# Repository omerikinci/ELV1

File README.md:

# ELV1 — Elektronik Kör Yük V1

Elektronik kör yük (electronic dummy load) cihazının ilk stabil versiyonu.
150 W ile sınırlandırılmış, 30 V / 10 A aralığını destekler.

Proje detayları ve görseller: https://omerikinci.com/projects/electronic-dummy-load

## İçerik

| Klasör | Açıklama |
| --- | --- |
| `firmware/` | STM32G030F6 için STM32CubeIDE projesi (`ilkdeneme`). Final kod: `firmware/Core/Src/main.c` |
| `firmware-history/2026-04-27-stable/` | 27.04.2026 tarihli önceki stabil `main.c` |
| `hardware/ELV1/` | KiCad şema ve PCB (`ELV1`, eski adıyla `Electronic Load`), PCB görselleri, projeye özel sembol kütüphanesi. Şema orijinal tasarımı gösterir; karttaki farklar aşağıda. |
| `hardware/ELV1-revision/` | ELV1'in revizyon kartı (tasarım aşamasında, STM32G071CBT6): KiCad şema ve PCB (`ELV1 revision`), G071 pin planı (`G071 pin plani.md`), firmware rehberi (`ELV1 revision - FIRMWARE REHBERI.txt`), görseller |
| `hardware/libraries/` | Projelerde kullanılan özel KiCad sembol (`symbols/`) ve footprint (`footprints/`) kütüphaneleri |
| `arduino-prototype/` | STM32'ye geçmeden önceki Arduino tabanlı ilk prototip (`koryukprojesi.ino`) |

## Firmware

- MCU: STM32G030F6Px
- ADS1115 (I2C) ile akım/gerilim ölçümü, dahili ADC
- DS18B20 sıcaklık sensörü
- I2C LCD, buzzer, soft-start

Derlemek için `firmware/` klasörünü STM32CubeIDE'ye mevcut proje olarak içe aktarın.

## ELV1'in final hali (şemadan farklar)

ELV1 ilk cihazdır ve bu haliyle kalır. Sorunlar anlaşıldıkça yalnızca düzeltme yapılır.
Yeni özellikler (USB/PC bağlantısı, pot yerine encoder vb.) ELV1 revision'a aittir.

`hardware/ELV1/ELV1.kicad_sch` **bilerek güncellenmedi**; orijinal tasarımı gösterir
(4 MOSFET, 4 x 0.1 Ω şönt, LM358). Karttaki gerçek durum:

| Parça | Şemada | Kartta | Tarih |
| --- | --- | --- | --- |
| Yük MOSFET'leri | U1, U6, U12, U13 (4 x IRFP260N) | Yalnız U1 ve U6. U12, U13 söküldü. | 10.2026 |
| Şöntler | R2, R23, R30, R45: 0.1 Ω 10 W (markasız) | R2 ve R23 yerinde: 2 x Isabellenhütte VMS-R100-1.0-U paralel = 0.05 Ω. R30, R45 söküldü. | 20.10.2026 |
| Op-amp'ler (U2, U3) | LM358 | OPA2197 | — |
| R1 (akım potu besleme direnci) | 440K | 440K olmalı (aşağıdaki nota bak) | 20.10.2026 |
| Şebeke X kondansatörü boşaltması | yok | 1 MΩ 1 W THT, AC girişte L-N arası | 20.10.2026 |

**Neden:**
- **Şöntler:**
  - Markasız 10 W dirençler ısındıkça akım kayıyordu. VMS'nin sıcaklık katsayısı < 20 ppm/K.
  - 2 MOSFET'te tek 0.1 Ω VMS, 5 A'de 2.5 W harcar; bu, 3 W sınırının %83'üdür ve direnç aşırı ısınıyordu.
  - Paralel çiftte direnç başına 0.625 W düşer (sınırın %21'i).
- **R1:**
  - Akımı pot ayarlar. Op-amp her şöntün gerilimini pot gerilimine eşitler, bu yüzden toplam akım = kanal sayısı x pot gerilimi / şönt direnci.
  - 2 x 0.1 Ω döneminde pot tam turda ~5 A veriyordu. Bu yüzden R1 geçici olarak 220K yapıldı.
  - 2 x 0.05 Ω ile 440K tekrar tam turda ~10 A verir; bu, orijinal 4 x 0.1 Ω ölçeğidir.
  - 220K ile tam tur ~20 A ister ve ISET % göstergesi yarı turda %100'e ulaşır.
- **Boşaltma direnci:**
  - Cihaz kapalıyken fiş çekilince EMI filtresinin X kondansatöründe kalan şarj çarpıyordu.
  - Önce geçici olarak 12 x 10 MΩ paralel (~790k) takıldı. Ancak paralel bağlı her direnç tam şebeke tepe gerilimini (~325 V) görür; 1/8 ve 1/4 W dirençler bu gerilim için uygun değil.
  - 20.10.2026'da bunların yerine tek 1 MΩ, 1 W, 500 V direnç (Royalohm MF02WJJ0105A19) takıldı.

**Durum (20.10.2026):** ELV1 tamamlandı. Bir sorun çıkmadıkça açılmayacak; geliştirme ELV1 revision'da sürüyor.

**Firmware'de buna göre ayarlananlar** (`firmware/Core/Src/main.c`):
- Akım, iki kanalın tek uçlu okumalarının toplamıdır: ADS1115 AIN0 (U1) + AIN1 (U6), `CURRENT_ADS_CH_MASK 0x03`.
  - ±0.512 V aralık, 250 SPS, kanal başına 8 örnek ortalaması.
  - Kelvin bağlantısı yok. Her kanal şöntle birlikte ortak GND yolunun düşümünü de görür. Bu düşüm `CURRENT_UV_PER_A 59172` (0.05 Ω + 2 x ~4.6 mΩ) katsayısının içindedir.
  - Kalibrasyon: seri multimetreyle ~5 A'de karşılaştır, yeni = 59172 x (ekrandaki / multimetredeki).
- Diğer ayarlar:
  - SET V düşük koruması 10 mA'den itibaren devrede.
  - Ekrandaki gerilimler kesilmez, yuvarlanır.
  - Güç koruması 160 W (MOSFET başına ~80 W).

**Ölçülen özellikler:**
- Ters polarite algılaması 1.71 V'ta devreye giriyor.

## ELV1 revision'ı başka bilgisayarda açmak (Windows / macOS)

1. Repoyu klonla:
   ```
   git clone https://github.com/omerikinci/ELV1.git
   ```
2. KiCad 10 ile `hardware/ELV1-revision/ELV1 revision.kicad_pro` dosyasını aç.
3. Özel kütüphaneler artık **global** tablodan yükleniyor (18.10.2026). Proje-içi
   `sym-lib-table` / `fp-lib-table` dosyaları kaldırıldı, çünkü global tabloda aynı
   isimler tanımlıyken KiCad çakışma uyarısı veriyordu.

   Yeni bir bilgisayarda kurulum: `hardware/libraries/` içeriğini kalıcı bir yere kopyala
   (bu makinede `~/Documents/Elektronik/Library/`), sonra KiCad'de
   **Preferences → Manage Symbol Libraries / Manage Footprint Libraries → Global**
   sekmesine şu isimlerle ekle:

   | Sembol kütüphanesi | Footprint kütüphanesi |
   | --- | --- |
   | `myCONN`, `myCPU`, `myDiodes`, `myIC`, `myNMOS`, `myNTC`, `mySW` | `myNTC`, `myTO247`, `myFuse` |

   Dikkat: eski isimler `my-NMOS` ve `mydiodes` kullanımdan kalktı; sırasıyla `myNMOS`
   ve `myDiodes` oldu. `hardware/libraries/` sürüm kontrolündeki asıl kaynaktır —
   global kopyayı ondan tazele, ters yönde değil.
4. Çalışmaya başlamadan önce `git pull`, bitirince `git add` / `git commit` / `git push` yap.
   İki bilgisayarda aynı anda aynı dosyayı düzenleme; KiCad dosyaları birleştirilemez.

Not: `*-backups/`, `*.kicad_prl`, `fp-info-cache` ve kilit dosyaları `.gitignore` ile dışarıda tutulur.

Bu makinedeki konum: `~/Documents/GitHub/ELV1-revision/` — GitHub Desktop'ın yönettiği
klasörde, `ELV2` deposunun yanında. Bu repo git üzerinden çalışılır; KiCad projeleri
`hardware/` altında.

`~/Documents/Elektronik/Projeler/ElectronicLoad/` orada duran ayrı bir kopyadır ve bu
repodaki `hardware/ELV1/` ile aynı kartın eski adıdır — hangisinin kalacağına karar
verilmedi.

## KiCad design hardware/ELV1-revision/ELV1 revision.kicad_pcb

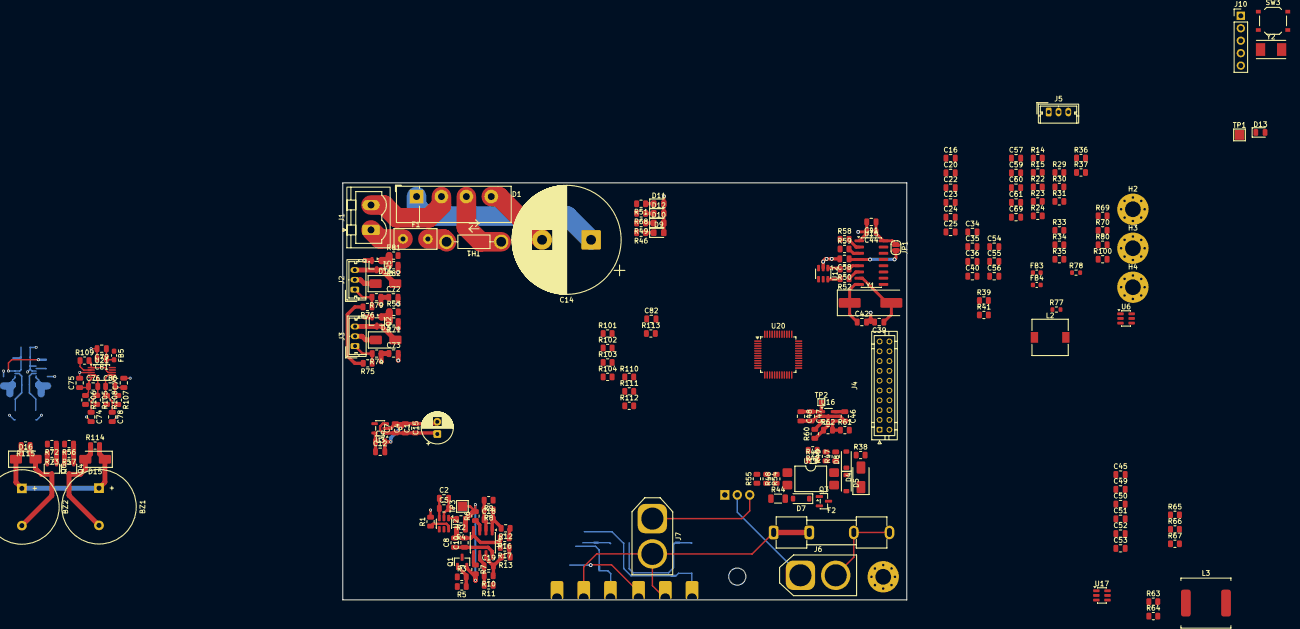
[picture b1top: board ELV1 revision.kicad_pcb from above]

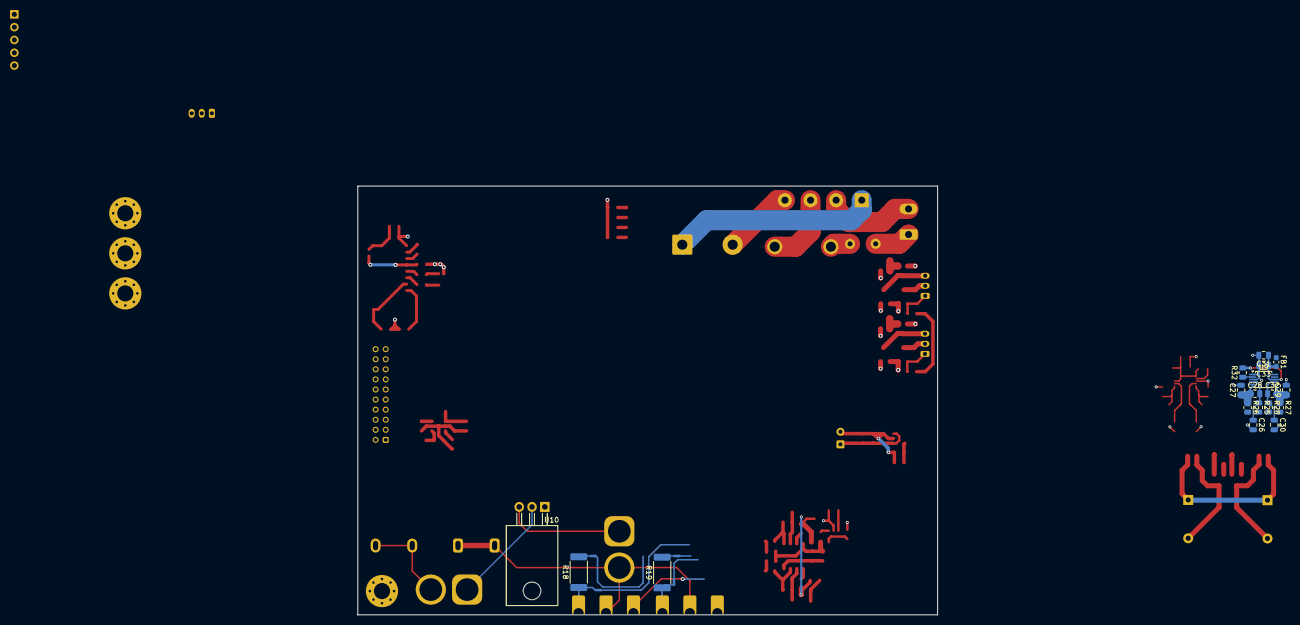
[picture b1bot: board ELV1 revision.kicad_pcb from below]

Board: 2 copper layers, 115.0 x 85.1 mm, 228 parts (22 on the bottom side), 124 nets.

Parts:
BZ1, BZ2: Passive Buzzer; Buzzer_15x7.5RM7.6
C1, C16, C31, C41, C45, C46, C48, C79: 10uF X7R; C_0805_2012Metric
C2: 10uF; C_0805_2012Metric
C4, C8, C9: 1uF X7R; C_0805_2012Metric
C5, C57, C59, C60, C69: 100nF; C_0805_2012Metric
C7, C10, C12, C20, C22, C33, C34, C35, C36, C40, C44, C47, C49, C50, C58, C81, C82: 100nF X7R; C_0805_2012Metric
C14: 6800uF; CP_Radial_D22.0mm_P10.00mm_SnapIn
C15: 100uF; CP_Radial_D6.3mm_P2.50mm
C18, C19, C72, C73: 10nF; C_0805_2012Metric
C23, C24, C51, C52: 22uF; C_0805_2012Metric
C25: 75pF; C_0805_2012Metric
C26, C27, C29, C30, C74, C75, C77, C78: 22nF X7R; C_0805_2012Metric
C28, C32, C76, C80: 220nF X7R; C_0805_2012Metric
C39, C42: 22pF NP0; C_0805_2012Metric
C53: 100pF; C_0805_2012Metric
C54, C55: 22pF; C_0805_2012Metric
C56: 1uF; C_0805_2012Metric
C61: 4.7uF; C_0805_2012Metric
D1: KBU8M; Diode_Bridge_Vishay_KBU
D3, D14, D15, D16: SS14; D_SMA
D4: 12V ZENER; D_SMA
D5, D7, D8: 1N4148W; D_SOD-123
D9, D10, D11, D12: RED LED; LED_0805_2012Metric_Pad1.15x1.40mm_HandSolder
D13: STATUS LED; LED_0805_2012Metric
F1: 2A Slow Blow; Fuse_Littelfuse_395Series
F2: 15A FUSE; Fuseholder_Clip-5x20mm_Keystone_3512_Inline_P23.62x7.27mm_D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
FB1, FB5: 600R 100MHz; L_0603_1608Metric_Pad1.05x0.95mm_HandSolder
FB3, FB4: 600R 100MHZ; L_0603_1608Metric
H1, H2, H3, H4: MountingHole_Pad; MountingHole_3.2mm_M3_Pad_Via
J1: 15VAC 30VA Transformer out; PhoenixContact_MSTBVA_2,5_2-G-5,08_1x02_P5.08mm_Vertical
J2: FAN1; Molex_Micro-Latch_53253-0370_1x03_P2.00mm_Vertical
J3: FAN2; Molex_Micro-Latch_53253-0370_1x03_P2.00mm_Vertical
J4: Conn_02x10_Odd_Even; JST_PHD_B20B-PHDSS_2x10_P2.00mm_Vertical
J5: DS18B20; Molex_Micro-Latch_53253-0370_1x03_P2.00mm_Vertical
J6, J7: power in (outside); AMASS_XT60-M_1x02_P7.20mm_Vertical
J10: PROGRAM PINS; PinHeader_1x05_P2.54mm_Vertical
JP1: SolderJumper_2_Open; SolderJumper-2_P1.3mm_Open_RoundedPad1.0x1.5mm
L2: 10uH; L_7.3x7.3_H4.5
L3: 15uH; L_SOREDE_SNR.1050_10x10x5mm
NT1, NT2, NT3, NT4: NetTie_2; NetTie-2_SMD_Pad0.5mm
Q1, Q2, Q3, Q5: IRLML6344TRPBF; SOT-23
Q4, Q6: IRLML6344TRPBF; SOT-23-3
R1, R2, R5, R16, R17, R29, R32, R34, R42, R57, R71, R73, R74, R75, R76, R79, R82, R100, R109: 10K; R_0805_2012Metric
R3, R12, R13, R25, R26, R27, R28, R40, R41, R56, R58, R59, R70, R72, R105, R106, R107, R108: 100R; R_0805_2012Metric
R4: 2.2K; R_0805_2012Metric
R6, R7, R9, R11, R30, R35, R36, R37, R49, R53, R61, R81, R114, R115: 1K; R_0805_2012Metric
R8, R10: 220K; R_0805_2012Metric
R14, R63: 511K; R_0805_2012Metric
R15, R64: 105K; R_0805_2012Metric
R18, R19: 0.1R SHUNT RESISTOR; R_2512_6332Metric_Pad1.40x3.35mm_HandSolder
R22, R65: 49.9R; R_0805_2012Metric
R23, R38, R48, R62, R66, R112: 100K; R_0805_2012Metric
R24: 13K; R_0805_2012Metric
R31, R33, R39, R51, R68, R69, R110, R111: 4.7K; R_0805_2012Metric
R44: 5.6K; R_1206_3216Metric
R45: 47K; R_0805_2012Metric
R46, R80: 330R; R_0805_2012Metric
R47: 100; R_0805_2012Metric
R50, R52: 22R; R_0805_2012Metric
R54, R101, R103: 47K 0.1%; R_0805_2012Metric
R55, R102, R104: 3.3K 0.1%; R_0805_2012Metric
R60: 3.3K; R_0805_2012Metric
R67: 5.23K; R_0805_2012Metric
R77, R78: 0R; R_0603_1608Metric
R113: 12K; R_0805_2012Metric
SW3: SW_Push; SW_Push_1P1T_XKB_TS-1187A
TH1: 0R; NTC
TP1, TP3: TestPoint; TestPoint_Pad_2.0x2.0mm
TP2: TestPoint; TestPoint_Pad_1.0x1.0mm
U2: MCP4725xxx-xCH; SOT-23-6
U3: AP2112K-3.3; SOT-23-5
U4: OPA2197xD; SOIC-8_3.9x4.9mm_P1.27mm
U6, U17: TPS54302; SOT-23-6
U7, U8: IRFP260NPBF; TO-247 Edge Castellated
U9, U21: ADS1115IDGS; TSSOP-10_3x3mm_P0.5mm
U10: IRFB4110PBF; TO-220-3_Horizontal_TabDown
U12: SRV05-4; SOT-23-6
U13: LTV-817S; SMDIP-4_W9.53mm
U15: CH340G; SOIC-16_3.9x9.9mm_P1.27mm
U16: SY6280AAC; SOT-23-5_HandSoldering
U20: STM32G071CBT6; LQFP-48_7x7mm_P0.5mm
Y1: 12MHZ CRYSTAL; Crystal_SMD_HC49-SD
Y2: ABM7-8.000MHZ-D2Y-T; Crystal_SMD_Abracon_ABM7-2Pin_6.0x3.5mm

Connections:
+3.3V: C2.1, C5.1, C9.1, C12.1, C41.1, C44.1, C59.1, FB1.1, FB3.1, FB4.2, FB5.1, J4.1, J4.16, J5.1, J10.1, JP1.1 (A), R5.2, R30.1, R31.2, R33.2, R34.2, R39.2, R42.1, R45.2, R46.2, R69.2, R75.2, R76.2, R100.2, R110.2, R111.2, U2.3 (VDD), U3.5 (VOUT), U15.16 (VCC), U20.4 (VBAT)
+5V: BZ1.1 (+), BZ2.1 (+), C1.1, C4.1, C7.1, C15.1, C23.1, C24.1, C46.1, D15.1 (K), D16.1 (K), J4.3, L2.2, R22.1, R49.2, R114.2, R115.2, U3.1 (VIN), U3.3 (EN), U16.5 (IN)
+12V: C8.1, C10.1, C51.1, C52.1, D3.1 (K), D14.1 (K), J2.2, J3.2, L3.2, R65.1, R68.2, U4.8 (V+)
/20V: C14.1, C16.1, C20.1, C45.1, C49.1, D1.1 (+), R14.1, R51.2, R63.1, R112.2, U6.3 (VIN), U17.3 (VIN)
/20V SENSE: C82.1, R112.1, R113.2, U20.11 (PA0)
/ADS2 VDD: C79.1, C81.1, FB5.2, R109.2, U21.1 (ADDR), U21.8 (VDD)
/AR0: NT1.1, R9.1, R25.2
/AR1: NT2.1, R26.2
/AR2: NT3.1, R11.1, R27.2
/AR3: NT4.1, R28.2
/BUZZER1: R56.2, U20.17 (PA6)
/BUZZER2: R72.2, U20.18 (PA7)
/D+: J4.10, R50.2, U12.1 (IO1)
/D-: J4.12, R52.2, U12.6 (IO4)
/DAC CONTROL: R3.1, U20.30 (PC6)
/DS18B20 DQ: R41.2, R70.1, U20.23 (PB11)
/ENDODER A: C35.1, R36.1, U20.25 (PB13)
/ENDODER B: C34.1, R35.1, U20.26 (PB14)
/ENDODER SW: C36.1, R37.1, U20.27 (PB15)
/FAN CONTROL 1: R81.2, U20.48 (PB9)
/FAN CONTROL 2: R53.2, U20.22 (PB10)
/G1: R12.1, R16.1, U7.1 (G)
/G2: R13.1, R17.1, U8.1 (G)
/I2C SCL: J4.5, R110.1, U2.5 (SCL), U9.10 (SCL), U20.33 (PA9/PA11), U21.10 (SCL)
/I2C SDA: J4.7, R111.1, U2.4 (SDA), U9.9 (SDA), U20.34 (PA10/PA12), U21.9 (SDA)
/LOAD VOLTAGE: C40.1, R54.1, R55.2, R105.2, R108.2, U20.14 (PA3)
/OUT CONTROL: R40.1, R42.2, U20.24 (PB12)
/RCP: R47.2, U20.13 (PA2)
/RESET BUTTON: J4.13, R29.1, U20.31 (PC7)
/RX: R58.1, U20.46 (PB7)
/TACT1: C72.1, R79.1, U20.43 (PB4)
/TACT2: C73.1, R74.1, U20.44 (PB5)
/TX: R59.1, U20.45 (PB6)
/USB 5V: C47.1, C48.1, J4.17, TP2.1 (1_1), U16.1 (OUT)
/USB CHARGE: R61.2, U20.37 (PA15)
/VCC LINE: F2.1, J7.2, R103.2, U7.2 (D), U8.2 (D)
/VLINE DIV: R103.1, R104.2, R107.2
/VS-: R101.1, R102.2, R106.2
GND: C1.2, C2.2, C4.2, C5.2, C7.2, C8.2, C9.2, C10.2, C12.2, C14.2, C15.2, C16.2, C20.2, C23.2, C24.2, C26.2, C27.2, C29.2, C30.2, C31.2, C33.2, C34.2, C35.2, C36.2, C39.2, C40.2, C41.2, C42.2, C44.2, C45.2, C46.2, C47.2, C48.2, C49.2, C51.2, C52.2, C54.1, C55.1, C56.2, C57.2, C58.2, C59.2, C60.2, C61.2, C69.2, C72.2, C73.2, C74.2, C75.2, C77.2, C78.2, C79.2, C81.2, C82.2, D1.4 (-), D4.2 (A), D9.2 (A), D10.2 (A), D11.2 (A), D12.2 (A), D13.1 (K), J4.8, J4.9, J4.14, J4.15, J4.19, J4.20, J5.3, J7.1, J10.5, NT2.2, NT4.2, Q1.3 (D), Q2.2 (S), Q3.3 (D), Q4.2 (S), Q5.2 (S), Q6.2 (S), R1.2, R4.2, R15.2, R16.2, R17.2, R18.2, R19.2, R24.2, R29.2, R55.1, R57.2, R60.1, R62.1, R64.2, R67.2, R71.1, R73.2, R82.1, R102.1, R104.1, R113.1, SW3.1, U2.2 (VSS), U3.2 (GND), U4.4 (V-), U6.1 (GND), U9.1 (ADDR), U9.3 (GND), U10.3 (S), U12.2 (VN), U13.3, U15.1 (GND), U16.2 (GND), U17.1 (GND), U20.7 (VSS), U21.3 (GND)
GND1: J6.1, R44.1, R101.2, U10.2 (D)
unnamed: BZ1.2 (-), D15.2 (A), Q4.3 (D), R114.1
unnamed: BZ2.2 (-), D16.2 (A), Q6.3 (D), R115.1
unnamed: C18.2, R8.1, R12.2, U4.1
unnamed: C19.2, R10.1, R13.2, U4.7
unnamed: C25.1, R22.2, R23.1
unnamed: C53.1, R65.2, R66.1
unnamed: C54.2, R77.1, Y2.2
unnamed: C55.2, R78.1, Y2.1
unnamed: D1.3, TH1.1
unnamed: D3.2 (A), J3.3, Q2.3 (D)
unnamed: D4.1 (K), D5.2 (A), Q3.2 (S), R38.1, U10.1 (G)
unnamed: D5.1 (K), D8.1 (K), U13.4
unnamed: D7.2 (A), R44.2
unnamed: D7.1 (K), R48.2, U13.1
unnamed: D8.2 (A), R45.1, R47.1
unnamed: D9.1 (K), R46.1
unnamed: D10.1 (K), R49.1
unnamed: D11.1 (K), R51.1
unnamed: D12.1 (K), R68.1
unnamed: D13.2 (A), R80.1
unnamed: D14.2 (A), J2.3, Q5.3 (D)
unnamed: F1.2, TH1.2
unnamed: F1.1, J1.1
unnamed: D1.2, J1.2
unnamed: J2.1, R76.1, R79.2
unnamed: J3.1, R74.2, R75.1
unnamed: J4.2, R31.1, R35.2
unnamed: J4.4, R33.1, R36.2
unnamed: J4.6, R34.1, R37.2
unnamed: J4.11, R30.2
unnamed: J4.18, R39.1, R41.1
unnamed: J5.2, R69.1, R70.2
unnamed: F2.2, J6.2, R48.1, R54.2, U13.2
unnamed: J10.2, U20.35 (PA13)
unnamed: J10.3, U20.36 (PA14)
unnamed: C69.1, J10.4, R100.1, SW3.2, U20.10 (PF2)
unnamed: C58.1, JP1.2 (B), U15.4 (V3)
unnamed: Q1.1 (G), R3.2, R5.1
unnamed: Q1.2 (S), R2.1, R4.1, R6.2, R7.2, TP3.1 (1_1)
unnamed: Q2.1 (G), R53.1, R71.2
unnamed: Q3.1 (G), R40.2
unnamed: Q4.1 (G), R56.1, R57.1
unnamed: Q5.1 (G), R81.1, R82.2
unnamed: Q6.1 (G), R72.1, R73.1
unnamed: R1.1, U2.6 (A0)
unnamed: R2.2, U2.1 (VOUT)
unnamed: R6.1, U4.3 (+)
unnamed: C18.1, R8.2, R9.2, U4.2 (-)
unnamed: R7.1, U4.5 (+)
unnamed: C19.1, R10.2, R11.2, U4.6 (-)
unnamed: C22.1, U6.6 (BOOT)
unnamed: R14.2, R15.1, U6.5 (EN)
unnamed: C25.2, R23.2, R24.1, U6.4 (FB)
unnamed: C22.2, L2.1, U6.2 (SW)
unnamed: NT1.2, R18.1, U7.3 (S)
unnamed: NT3.2, R19.1, U8.3 (S)
unnamed: C26.1, C28.2, R25.1, U9.4 (AIN0)
unnamed: C27.1, C28.1, R26.1, U9.5 (AIN1)
unnamed: C29.1, C32.2, R27.1, U9.6 (AIN2)
unnamed: C30.1, C32.1, R28.1, U9.7 (AIN3)
unnamed: R32.1, U9.2 (ALERT/RDY)
unnamed: C31.1, C33.1, FB1.2, R32.2, U9.8 (VDD)
unnamed: R59.2, U15.3 (RXD)
unnamed: R58.2, U15.2 (TXD)
unnamed: R50.1, U15.5 (UD+)
unnamed: R52.1, U15.6 (UD-)
unnamed: C39.1, U15.7 (XI), Y1.2
unnamed: C42.1, U15.8 (XO), Y1.1
unnamed: R61.1, R62.2, U16.4 (EN)
unnamed: R60.2, U16.3 (ISET)
unnamed: C50.1, U17.6 (BOOT)
unnamed: R63.2, R64.1, U17.5 (EN)
unnamed: C53.2, R66.2, R67.1, U17.4 (FB)
unnamed: C50.2, L3.1, U17.2 (SW)
unnamed: R80.2, U20.19 (PB0)
unnamed: R77.2, U20.8 (PF0)
unnamed: R78.2, U20.9 (PF1)
unnamed: C60.1, C61.1, FB4.1, TP1.1 (1_1), U20.6 (VDD)
unnamed: C56.1, C57.1, FB3.2, U20.5 (VREF+)
unnamed: C74.1, C76.2, R105.1, U21.4 (AIN0)
unnamed: C75.1, C76.1, R106.1, U21.5 (AIN1)
unnamed: C77.1, C80.2, R107.1, U21.6 (AIN2)
unnamed: C78.1, C80.1, R108.1, U21.7 (AIN3)
unnamed: R109.1, U21.2 (ALERT/RDY)

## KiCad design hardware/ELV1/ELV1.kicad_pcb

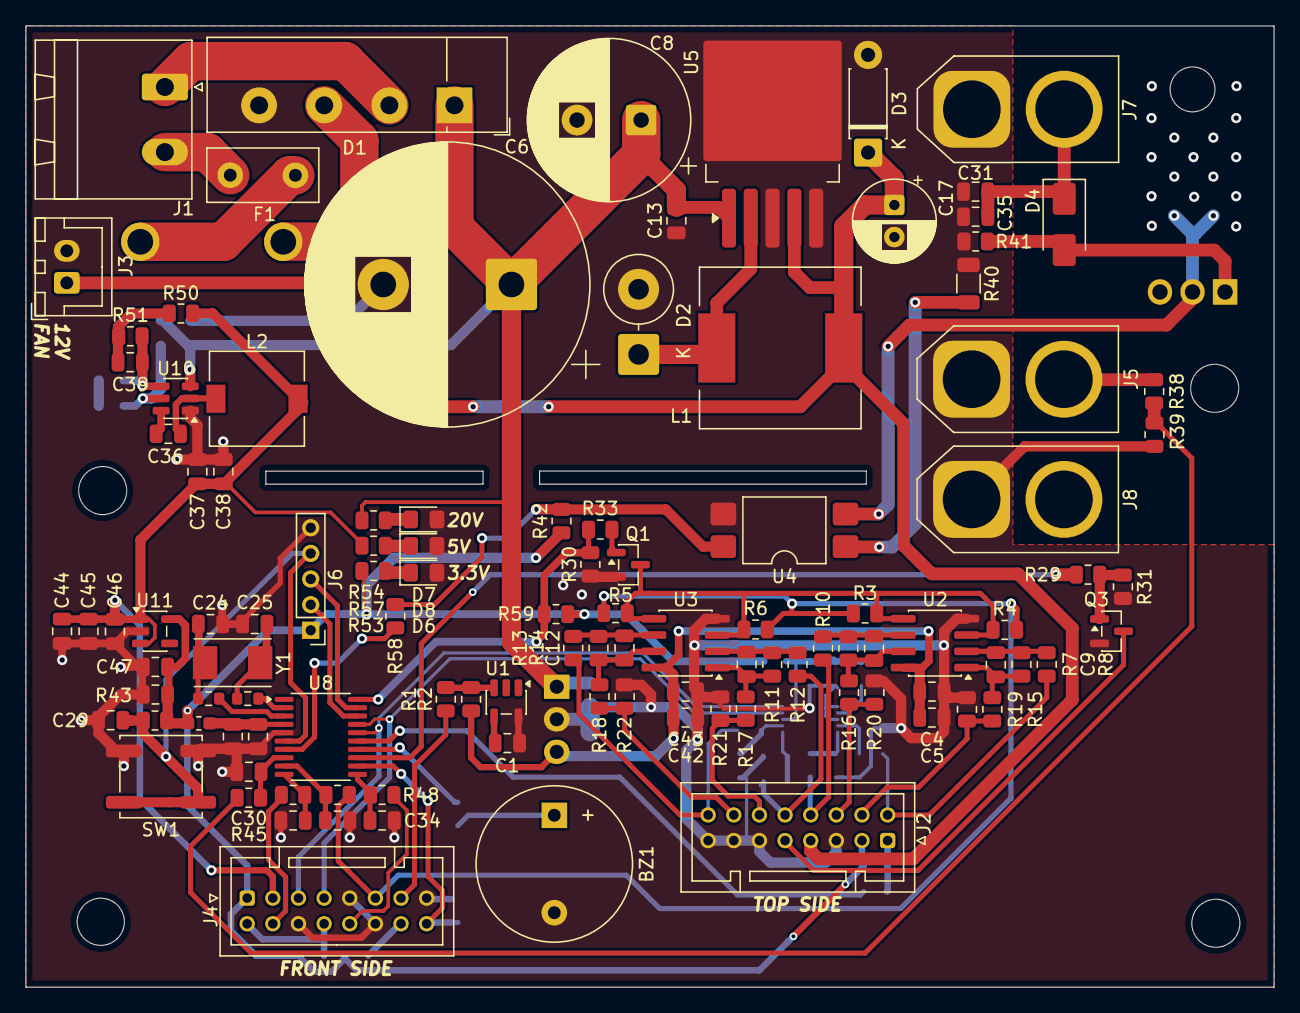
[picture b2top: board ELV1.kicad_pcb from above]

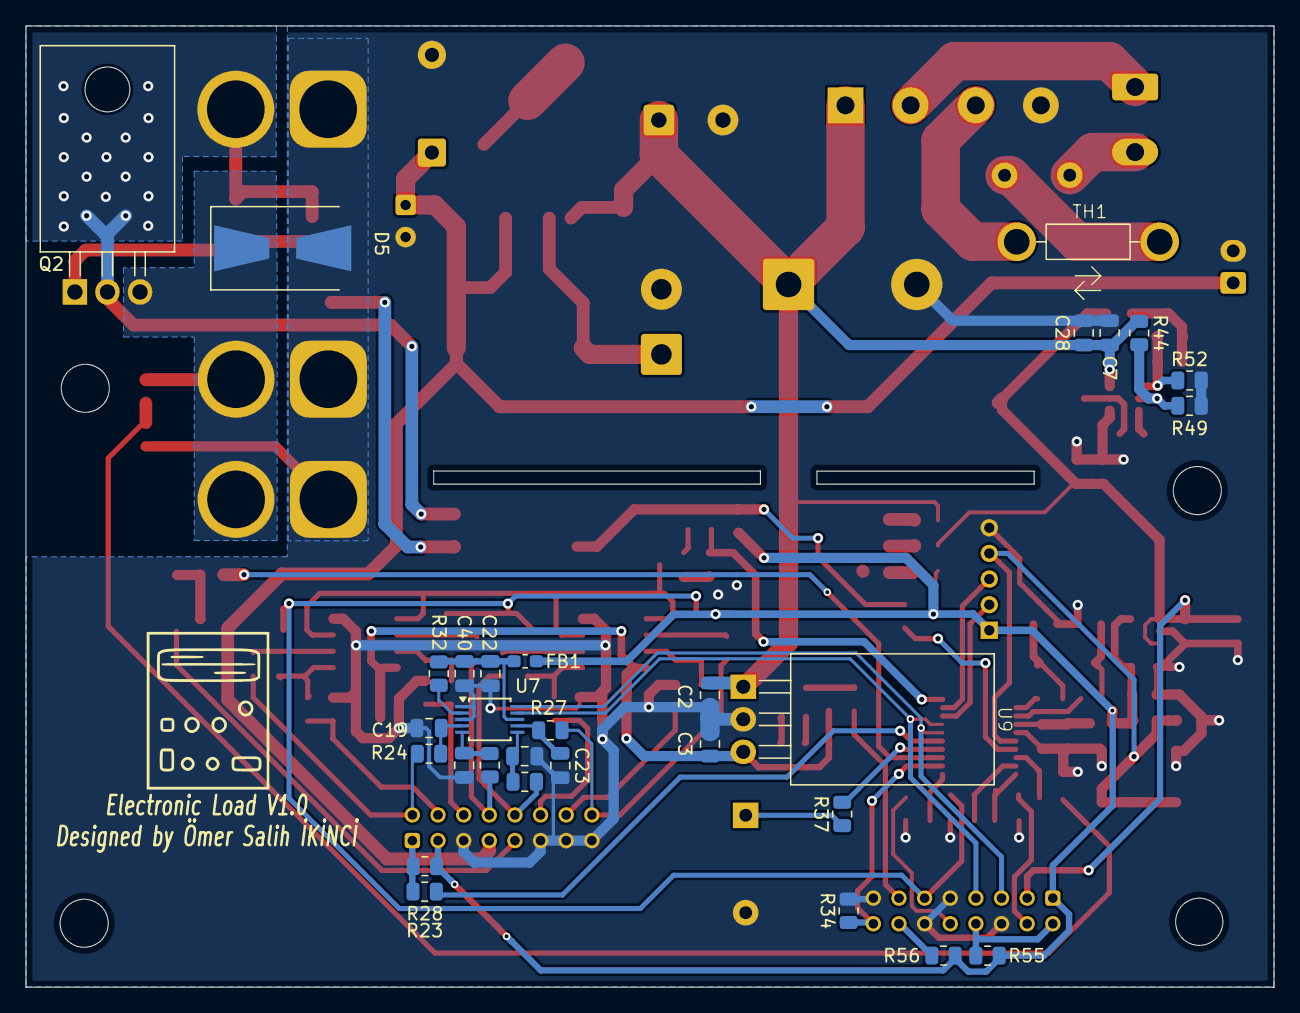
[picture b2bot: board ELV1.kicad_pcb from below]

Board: 2 copper layers, 97.3 x 75.0 mm, 140 parts (30 on the bottom side), 81 nets.

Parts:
BZ1: Buzzer; Buzzer_12x9.5RM7.6
C1, C26, C28, C40, C44: 10uF X7R; C_0805_2012Metric
C2, C3, C5, C7, C13, C19, C20, C21, C22, C23, C27, C29, C30, C32, C33, C34, C36, C42, C45, C48: 100nF X7R; C_0805_2012Metric
C4, C31, C43, C46, C47: 1uF X7R; C_0805_2012Metric
C6: 6800uF; CP_Radial_D22.0mm_P10.00mm_SnapIn
C8: 680uF 50V; CP_Radial_D12.5mm_P5.00mm
C9, C10, C11, C12: 1nF; C_0805_2012Metric
C17: 220uF 25V; CP_Radial_D6.3mm_P2.50mm
C24, C25: 18pF; C_0805_2012Metric
C35: 100nF 63V; C_0805_2012Metric
C37, C38: 22uF; C_0805_2012Metric
C39: 75pF; C_0805_2012Metric
D1: KBU8M; Diode_Bridge_Vishay_KBU
D2: 1N5822; D_DO-201AD_P5.08mm_Vertical_KathodeUp
D3: 1N4007; D_DO-41_SOD81_P7.62mm_Horizontal
D4: 12V ZENER; D_SMA
D5: SMCJ33CA-TKS; D_SMB-SMC_Universal_Handsoldering
D6, D7, D8: RED LED; LED_0805_2012Metric_Pad1.15x1.40mm_HandSolder
F1: 2A Slow Blow; Fuse_Littelfuse_395Series
FB1, FB2: 600R 100MHz; L_0603_1608Metric_Pad1.05x0.95mm_HandSolder
J1: 15VAC Transformer out; PhoenixContact_MSTBA_2,5_2-G-5,08_1x02_P5.08mm_Horizontal
J2: Top Panel; JST_PUD_B16B-PUDSS_2x08_P2.00mm_Vertical
J3: FAN OUT; JST_XH_B2B-XH-A_1x02_P2.50mm_Vertical
J4: Front Panel; JST_PUD_B16B-PUDSS_2x08_P2.00mm_Vertical
J5: power in (inside); AMASS_XT60-M_1x02_P7.20mm_Vertical
J6: Program Pins; PinHeader_1x05_P2.00mm_Vertical
J7: power in (outside); AMASS_XT60-M_1x02_P7.20mm_Vertical
J8: power in (outside) for batteries; AMASS_XT60-M_1x02_P7.20mm_Vertical
L1: 33uH; L_12x12mm_H8mm
L2: 10uH; L_7.3x7.3_H4.5
Q1, Q3: IRLML6344TRPBF; SOT-23
Q2: IRF4905; TO-220F-3_Horizontal_TabDown
R1: 22K; R_0805_2012Metric
R2, R19, R20, R21, R22, R30, R31, R32, R34, R42, R43, R59: 10K; R_0805_2012Metric
R3, R4, R5, R6, R8, R10, R12, R14, R24, R25, R26, R27, R41, R45, R46, R47, R48, R54, R55, R56: 1K; R_0805_2012Metric
R7, R9, R11, R13: 220K; R_0805_2012Metric
R15, R16, R17, R18, R23, R33, R37, R57: 100R; R_0805_2012Metric
R28: 4.7K; R_0805_2012Metric
R29, R58: 100; R_0805_2012Metric
R35, R36: 0R; R_0603_1608Metric
R38: 470K; R_0805_2012Metric
R39: 33K; R_0805_2012Metric
R40: 5.6K; R_1206_3216Metric
R44: 511K; R_0805_2012Metric
R49: 105K; R_0805_2012Metric
R50: 49.9R; R_0805_2012Metric
R51: 100K; R_0805_2012Metric
R52: 13.3K; R_0805_2012Metric
R53: 10R; R_0805_2012Metric
SW1: SW_Push_1P1T_NO_CK_KSC7xxJ
TH1: NTC 10R; NTC
U1: TL431DBV; SOT-23-5
U2, U3: LM358; SOIC-8_3.9x4.9mm_P1.27mm
U4: LTV-817S; SMDIP-4_W9.53mm
U5: LM2596S-12; TO-263-5_TabPin3
U7: ADS1115IDGS; TSSOP-10_3x3mm_P0.5mm
U8: STM32G030F6Px; TSSOP-20_4.4x6.5mm_P0.65mm
U9: LM7815_TO220; myto220
U10: TPS54302; SOT-23-6
U11: AP2112K-3.3; SOT-23-5
Y1: 8mHz; Crystal_SMD_Abracon_ABM7-2Pin_6.0x3.5mm

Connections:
/3.3V: C47.1, C48.1, FB1.1, FB2.1, J2.3, J4.1, J6.1, R28.1, R42.2, R43.2, R53.2, R55.1, R56.1, R59.1, U11.5 (VOUT)
/5V: C37.1, C38.1, C44.1, C45.1, C46.1, J4.3, L2.2, R50.1, R57.2, U11.1 (VIN), U11.3 (EN)
/20V: C2.1, C6.1, C7.1, C8.1, C13.1, C28.1, D1.1 (+), R44.1, R54.2, U5.1 (VIN), U9.1 (VI), U10.3 (VIN)
/A POT SIGNAL: J4.11, R3.2, R4.2, R5.2, R6.2, R46.2
/A POT VCC: J4.13, R1.1
/ADS1115/SCREEN SCL: J4.5, U7.10 (SCL), U8.16 (PA9/PA11)
/ADS1115/SCREEN SDA: J4.7, U7.9 (SDA), U8.17 (PA10/PA12)
/AR0: J2.2, R8.1, R24.2
/AR1: J2.8, R10.1, R25.2
/AR2: J2.10, R12.1, R26.2
/AR3: J2.16, R14.1, R27.2
/BUZZER: R37.2, U8.14 (PA7)
/DRAIN SIDE: C31.1, C35.1, D4.1 (K), J7.2, Q2.2 (D), U4.2
/DS18B20 DQ: R23.2, U8.15 (PA8/PB0/PB1/PB2)
/FAN CONTROL: R29.2, U8.13 (PA6)
/FAN SIGNAL: J2.9, Q3.3 (D)
/FAN VCC: C17.1, D3.1 (K), J2.7, J3.1, L1.2, U5.4 (FB)
/G1: J2.4, R15.1, R19.1
/G2: J2.6, R16.1, R20.1
/G3: J2.12, R17.1, R21.1
/G4: J2.14, R18.1, R22.1
/LOAD VOLTAGE: R38.1, R39.2, R45.2
/OCS: Q1.3 (D), R3.1, R4.1, R5.1, R6.1, U2.3 (+), U2.5 (+), U3.3 (+), U3.5 (+)
/OPAMP CONTROL: R30.1, R33.1, R59.2, U8.20 (PB3/PB4/PB5/PB6)
/Opamp VCC: C3.1, C4.1, C5.1, C42.1, C43.1, R2.1, U2.8 (V+), U3.8 (V+), U9.3 (VO)
/RCP: R58.2, U8.7 (PA0)
/RESET BUTTON: J4.16, R34.1, U8.12 (PA5)
/SET C POT: J4.10, R48.2
/SET V POT: J4.4, R47.2
/SOURCE SIDE: D5.1 (A1), J5.2, J8.2, Q2.3 (S), R38.2
GND: BZ1.2 (-), C1.2, C2.2, C3.2, C4.2, C5.2, C6.2, C7.2, C8.2, C13.2, C17.2, C19.2, C20.2, C21.2, C22.2, C23.2, C24.1, C25.1, C26.2, C27.2, C28.2, C29.2, C30.2, C31.2, C32.2, C33.2, C34.2, C35.2, C37.2, C38.2, C40.2, C42.2, C43.2, C44.2, C45.2, C46.2, C47.2, C48.2, D1.4 (-), D2.2 (A), D3.2 (A), D5.2 (A2), D6.2 (A), D7.2 (A), D8.2 (A), J2.5, J2.11, J2.13, J2.15, J3.2, J4.6, J4.9, J4.12, J4.15, J5.1, J6.5, J7.1, J8.1, Q1.2 (S), Q3.2 (S), R19.2, R20.2, R21.2, R22.2, R30.2, R31.1, R34.2, R39.1, R40.1, R41.1, R49.2, R52.2, SW1.2, U1.5 (A), U2.4 (V-), U3.4 (V-), U4.3, U5.3 (GND), U5.5 (~ON/OFF), U7.1 (ADDR), U7.3 (GND), U8.5 (VSS), U9.2 (GND), U10.1 (GND), U11.2 (GND)
unnamed: BZ1.1 (+), R37.1
unnamed: C9.2, R7.1, R15.2, U2.1
unnamed: C10.2, R9.1, R16.2, U2.7
unnamed: C11.2, R11.1, R17.2, U3.1
unnamed: C12.2, R13.1, R18.2, U3.7
unnamed: C24.2, R35.1, Y1.2
unnamed: C25.2, R36.1, Y1.1
unnamed: C39.1, R50.2, R51.1
unnamed: D1.3, TH1.1
unnamed: D2.1 (K), L1.1, U5.2 (OUT)
unnamed: D4.2 (A), Q2.1 (G), R41.2
unnamed: D6.1 (K), R53.1
unnamed: D7.1 (K), R54.1
unnamed: D8.1 (K), R57.1
unnamed: F1.2, TH1.2
unnamed: D1.2, J1.1
unnamed: F1.1, J1.2
unnamed: J2.1, R23.1, R28.2
unnamed: J4.2, J4.8, R55.2
unnamed: J4.14, R56.2
unnamed: J6.2, U8.18 (PA13)
unnamed: J6.3, U8.19 (PA14/PA15)
unnamed: C29.1, J6.4, R43.1, SW1.1, U8.6 (NRST)
unnamed: Q1.1 (G), R33.2
unnamed: Q3.1 (G), R29.1, R31.2
unnamed: R40.2, U4.1
unnamed: R42.1, R58.1, U4.4
unnamed: R1.2, R2.2, U1.3 (K)
unnamed: C1.1, U1.4 (REF)
unnamed: C9.1, R7.2, R8.2, U2.2 (-)
unnamed: C10.1, R9.2, R10.2, U2.6 (-)
unnamed: C11.1, R11.2, R12.2, U3.2 (-)
unnamed: C12.1, R13.2, R14.2, U3.6 (-)
unnamed: C19.1, R24.1, U7.4 (AIN0)
unnamed: C20.1, R25.1, U7.5 (AIN1)
unnamed: C21.1, R26.1, U7.6 (AIN2)
unnamed: C23.1, R27.1, U7.7 (AIN3)
unnamed: R32.1, U7.2 (ALERT/RDY)
unnamed: C22.1, C40.1, FB1.2, R32.2, U7.8 (VDD)
unnamed: C30.1, R45.1, U8.8 (PA1)
unnamed: C32.1, R46.1, U8.9 (PA2)
unnamed: C33.1, R47.1, U8.10 (PA3)
unnamed: C34.1, R48.1, U8.11 (PA4)
unnamed: R36.2, U8.2 (PB9/PC14)
unnamed: R35.2, U8.3 (PC15)
unnamed: C26.1, C27.1, FB2.2, U8.4 (VDD)
unnamed: C36.1, U10.6 (BOOT)
unnamed: R44.2, R49.1, U10.5 (EN)
unnamed: C39.2, R51.2, R52.1, U10.4 (FB)
unnamed: C36.2, L2.1, U10.2 (SW)

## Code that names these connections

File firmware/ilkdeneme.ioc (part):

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Mcu.Name=STM32G030F6Px
Mcu.Package=TSSOP20
Mcu.UserName=STM32G030F6Px
PA0.Mode=IN0
PA0.Signal=ADC1_IN0
PA1.Mode=IN1
PA1.Signal=ADC1_IN1
PA11\ [PA9].Mode=I2C
PA11\ [PA9].Signal=I2C2_SCL
PA12\ [PA10].Mode=I2C
PA12\ [PA10].Signal=I2C2_SDA
PA13.Mode=Serial_Wire
PA13.Signal=SYS_SWDIO
PA14-BOOT0.Mode=Serial_Wire
PA14-BOOT0.Signal=SYS_SWCLK
PA14-BOOT0__PA15.StandardMode=true
PA2.Mode=IN2
PA2.Signal=ADC1_IN2
PA3.Mode=IN3
PA3.Signal=ADC1_IN3
PA4.Signal=SharedAnalog_PA4
PA5.Mode=IN5
PA5.Signal=ADC1_IN5
PA6.Signal=GPIO_Output
PA7.Signal=GPIO_Output
PB0.Signal=GPIO_Output
PB0__PB1__PB2__PA8.StandardMode=true
PB3.Signal=GPIO_Output
PB3__PB4__PB5__PB6.StandardMode=true
PB7.Mode=IN11
PB7.Signal=ADC1_IN11
PB7__PB8.StandardMode=true
PC14-OSC32_IN\ (PC14)__PB9.StandardMode=true
RCC.HSE_VALUE=8000000
RCC.SYSCLKFreq_VALUE=16000000
board=custom
